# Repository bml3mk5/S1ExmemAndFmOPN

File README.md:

# Extended RAM & FM Synthesis Card for HITACHI MB-S1

This is the extension card for HITACHI MB-S1 and Limelight. This is assembled two circuits
which are extended RAMs and FM Synthesis (YAMAHA YM2203(OPN)). You can use two circuits, or just one of them.

## Used Tools

* KiCAD Version 5

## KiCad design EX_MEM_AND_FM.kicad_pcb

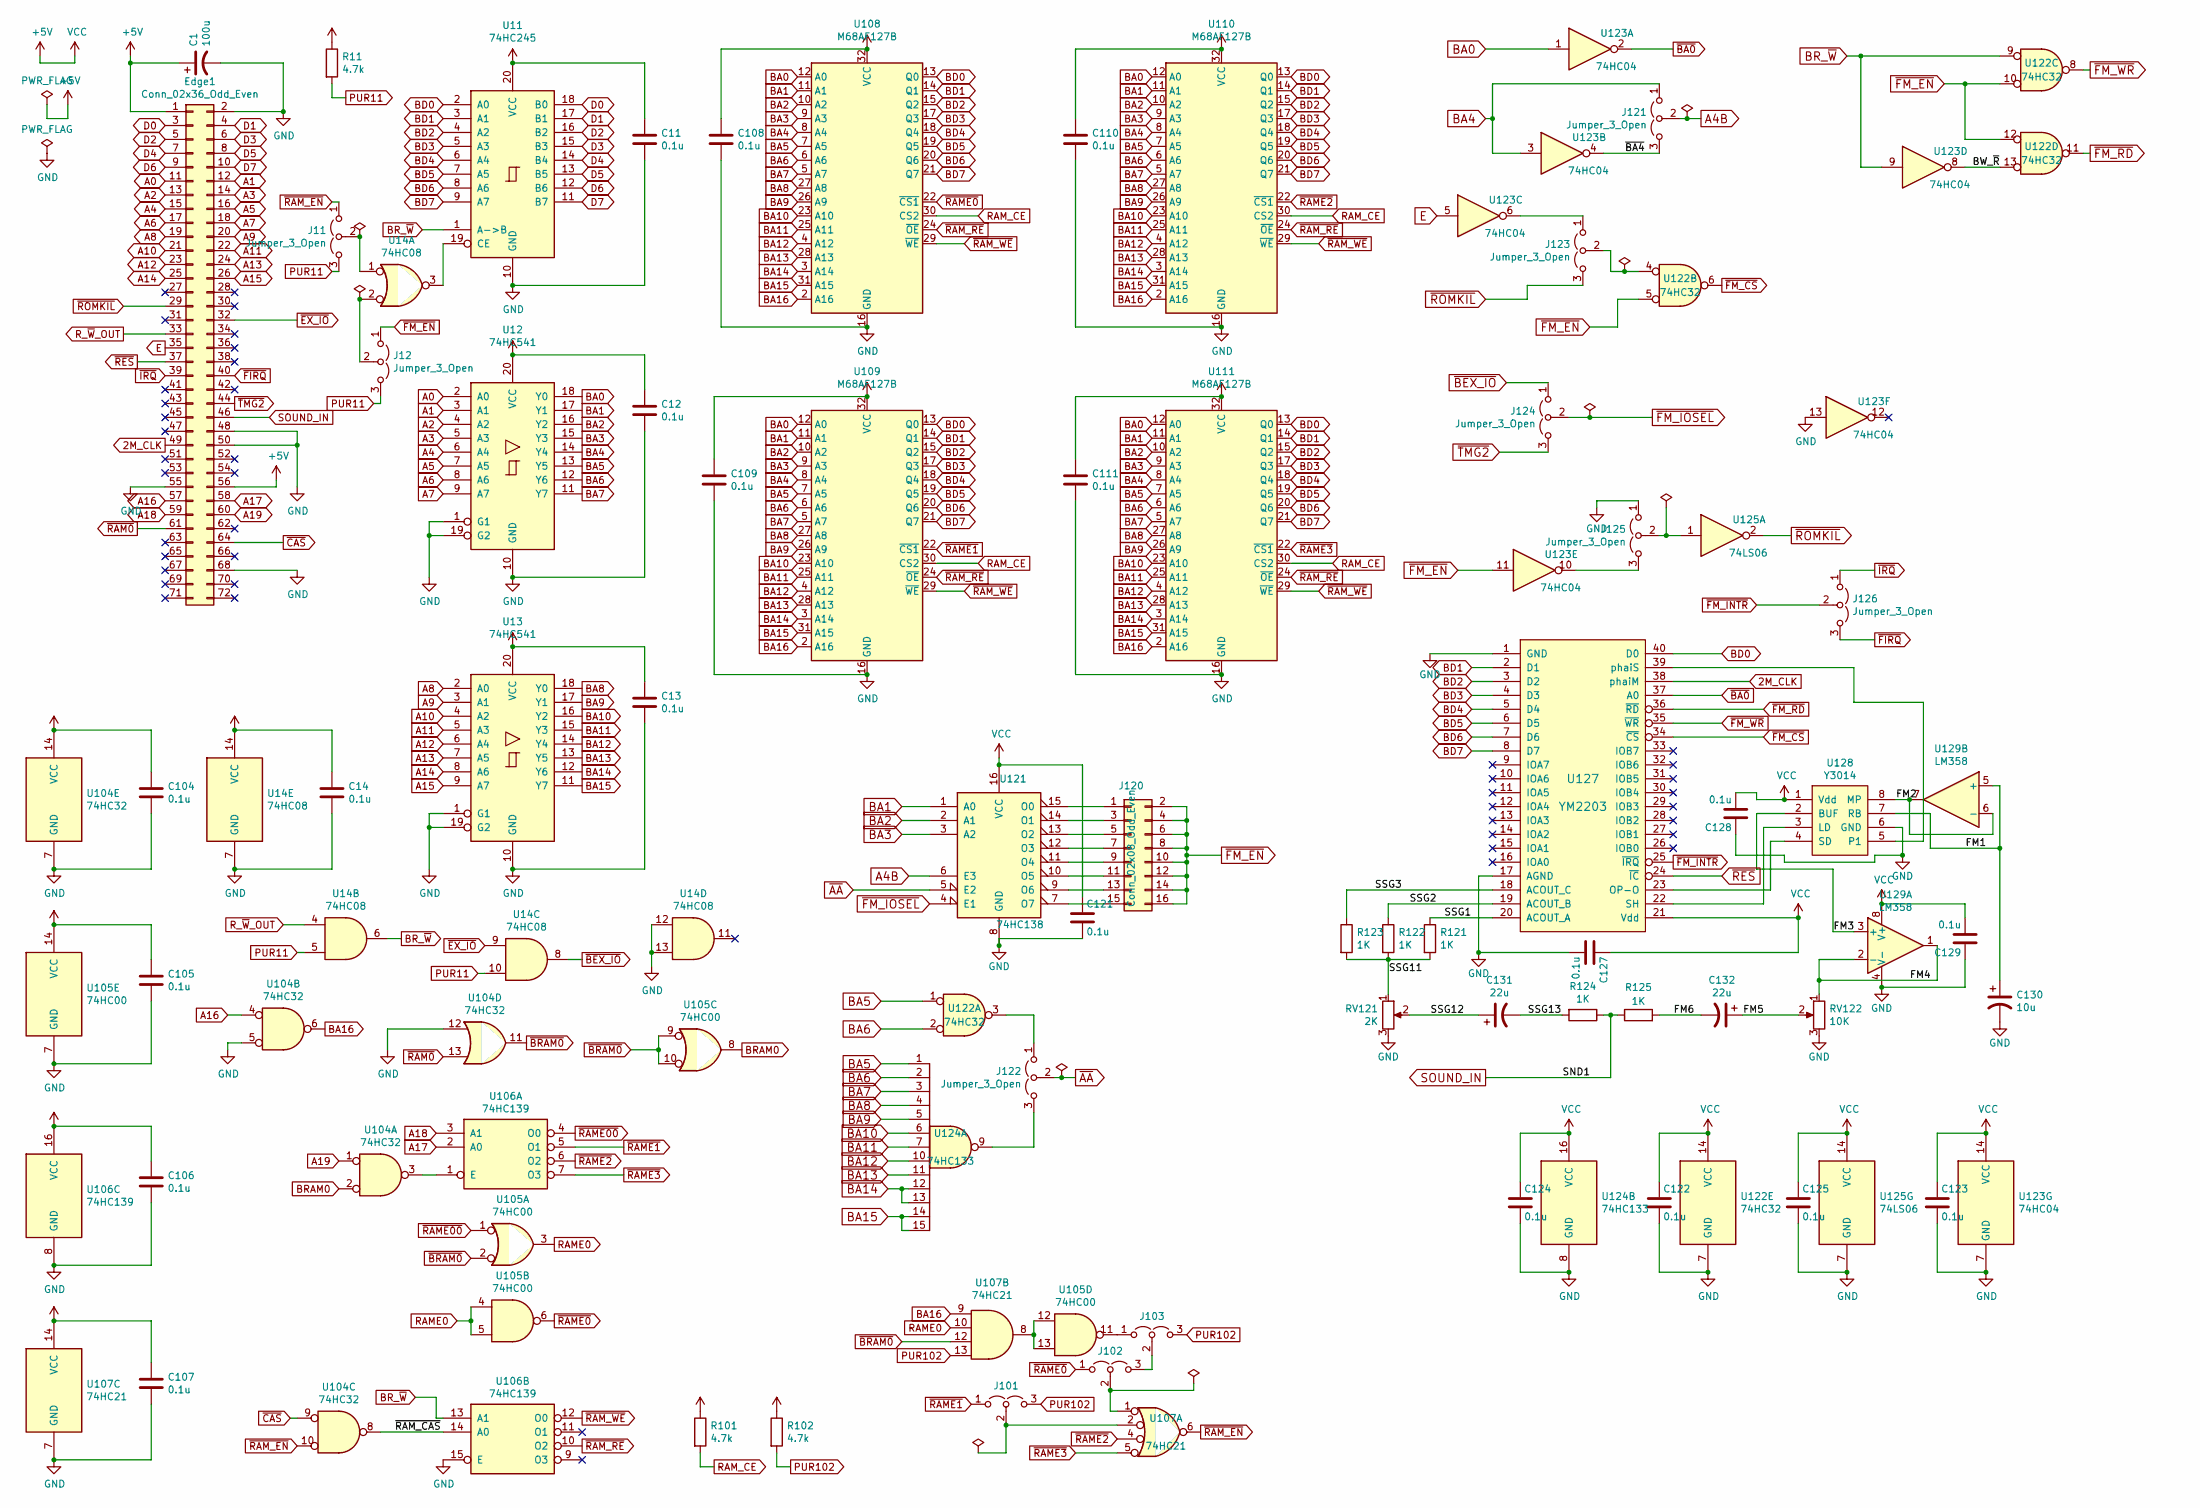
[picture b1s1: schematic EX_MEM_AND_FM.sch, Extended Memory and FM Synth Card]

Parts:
C1: 100u; CP_Radial_D6.3mm_P2.50mm
C11, C12, C13, C14, C104, C105, C106, C107, C108, C109, C110, C111, C121, C122, C123, C124, C125, C127, C128, C129: 0.1u; C_Disc_D3.0mm_W2.0mm_P2.50mm
C130: 10u; CP_Radial_D5.0mm_P2.50mm
C131, C132: 22u; CP_Radial_D5.0mm_P2.50mm
Edge1: Conn_02x36_Odd_Even; CardEdge72
J11, J12, J101, J102, J103, J121, J122, J123, J124, J125, J126: Jumper_3_Open; Pin_Header_Straight_1x03_Pitch2.54mm
J120: Conn_02x08_Odd_Even; Pin_Header_Straight_2x08_Pitch2.54mm
R11, R101, R102: 4.7k; R_Axial_DIN0204_L3.6mm_D1.6mm_P2.54mm_Vertical
R121, R122, R123, R124, R125: 1K; R_Axial_DIN0204_L3.6mm_D1.6mm_P2.54mm_Vertical
RV121: 2K; Potentiometer_Trimmer_Bourns_3339P_Horizontal
RV122: 10K; Potentiometer_Trimmer_Bourns_3339P_Horizontal
U11: 74HC245; DIP-20_W7.62mm
U12, U13: 74HC541; DIP-20_W7.62mm
U14: 74HC08; DIP-14_W7.62mm
U104, U122: 74HC32; DIP-14_W7.62mm
U105: 74HC00; DIP-14_W7.62mm
U106: 74HC139; DIP-16_W7.62mm
U107: 74HC21; DIP-14_W7.62mm
U108, U109, U110, U111: M68AF127B; SOIC-32
U121: 74HC138; DIP-16_W7.62mm
U123: 74HC04; DIP-14_W7.62mm
U124: 74HC133; DIP-16_W7.62mm
U125: 74LS06; DIP-14_W7.62mm
U127: YM2203; DIP-40_W15.24mm_Socket
U128: Y3014; DIP-8_W7.62mm_Socket
U129: LM358; DIP-8_W7.62mm_Socket

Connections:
2M_CLK: Edge1.49, U127.38 (phaiM)
+5V: C1.1, C11.1, C12.1, C13.1, C14.1, C104.1, C105.1, C106.1, C107.1, C108.1, C109.1, C110.1, C111.1, C121.1, C122.1, C123.1, C124.1, C125.1, C127.1, C128.2, C129.2, Edge1.1, Edge1.56, R11.1, R101.1, R102.1, U11.20 (VCC), U12.20 (VCC), U13.20 (VCC), U14.14 (VCC), U104.14 (VCC), U105.14 (VCC), U106.16 (VCC), U107.14 (VCC), U108.32 (VCC), U109.32 (VCC), U110.32 (VCC), U111.32 (VCC), U121.16 (VCC), U122.14 (VCC), U123.14 (VCC), U124.16 (VCC), U125.14 (VCC), U127.21 (Vdd), U128.1 (Vdd), U129.8 (V+)
/BW_~R~: U122.13, U123.8
/FM1: C130.1, U128.7 (RB), U129.5 (+)
/FM2: U128.8 (MP), U129.6 (-), U129.7
/FM3: U128.2 (BUF), U129.3 (+)
/FM4: RV122.1, U129.1, U129.2 (-)
/FM5: C132.1, RV122.2
/FM6: C132.2, R125.2
/SSG1: R121.1, U127.20 (ACOUT_A)
/SSG2: R122.1, U127.19 (ACOUT_B)
/SSG3: R123.1, U127.18 (ACOUT_C)
/SSG11: R121.2, R122.2, R123.2, RV121.1
/SSG12: C131.1, RV121.2
/SSG13: C131.2, R124.2
/~BA4: J121.3 (B), U123.4
/~RAM_CAS: U104.8, U106.14 (A0)
A0: Edge1.11, U12.2 (A0)
A1: Edge1.12, U12.3 (A1)
A2: Edge1.13, U12.4 (A2)
A3: Edge1.14, U12.5 (A3)
A4: Edge1.15, U12.6 (A4)
A4B: J121.2 (C), U121.6 (E3)
A5: Edge1.16, U12.7 (A5)
A6: Edge1.17, U12.8 (A6)
A7: Edge1.18, U12.9 (A7)
A8: Edge1.19, U13.2 (A0)
A9: Edge1.20, U13.3 (A1)
A10: Edge1.21, U13.4 (A2)
A11: Edge1.22, U13.5 (A3)
A12: Edge1.23, U13.6 (A4)
A13: Edge1.24, U13.7 (A5)
A14: Edge1.25, U13.8 (A6)
A15: Edge1.26, U13.9 (A7)
A16: Edge1.57, U104.4
A17: Edge1.58, U106.2 (A0)
A18: Edge1.59, U106.3 (A1)
A19: Edge1.60, U104.1
BA0: U12.18 (Y0), U108.12 (A0), U109.12 (A0), U110.12 (A0), U111.12 (A0), U123.1
BA1: U12.17 (Y1), U108.11 (A1), U109.11 (A1), U110.11 (A1), U111.11 (A1), U121.1 (A0)
BA2: U12.16 (Y2), U108.10 (A2), U109.10 (A2), U110.10 (A2), U111.10 (A2), U121.2 (A1)
BA3: U12.15 (Y3), U108.9 (A3), U109.9 (A3), U110.9 (A3), U111.9 (A3), U121.3 (A2)
BA4: J121.1 (A), U12.14 (Y4), U108.8 (A4), U109.8 (A4), U110.8 (A4), U111.8 (A4), U123.3
BA5: U12.13 (Y5), U108.7 (A5), U109.7 (A5), U110.7 (A5), U111.7 (A5), U122.1, U124.1
BA6: U12.12 (Y6), U108.6 (A6), U109.6 (A6), U110.6 (A6), U111.6 (A6), U122.2, U124.2
BA7: U12.11 (Y7), U108.5 (A7), U109.5 (A7), U110.5 (A7), U111.5 (A7), U124.3
BA8: U13.18 (Y0), U108.27 (A8), U109.27 (A8), U110.27 (A8), U111.27 (A8), U124.4
BA9: U13.17 (Y1), U108.26 (A9), U109.26 (A9), U110.26 (A9), U111.26 (A9), U124.5
BA10: U13.16 (Y2), U108.23 (A10), U109.23 (A10), U110.23 (A10), U111.23 (A10), U124.6
BA11: U13.15 (Y3), U108.25 (A11), U109.25 (A11), U110.25 (A11), U111.25 (A11), U124.7
BA12: U13.14 (Y4), U108.4 (A12), U109.4 (A12), U110.4 (A12), U111.4 (A12), U124.10
BA13: U13.13 (Y5), U108.28 (A13), U109.28 (A13), U110.28 (A13), U111.28 (A13), U124.11
BA14: U13.12 (Y6), U108.3 (A14), U109.3 (A14), U110.3 (A14), U111.3 (A14), U124.12, U124.13
BA15: U13.11 (Y7), U108.31 (A15), U109.31 (A15), U110.31 (A15), U111.31 (A15), U124.14, U124.15
BA16: U104.6, U107.9, U108.2 (A16), U109.2 (A16), U110.2 (A16), U111.2 (A16)
BD0: U11.2 (A0), U108.13 (Q0), U109.13 (Q0), U110.13 (Q0), U111.13 (Q0), U127.40 (D0)
BD1: U11.3 (A1), U108.14 (Q1), U109.14 (Q1), U110.14 (Q1), U111.14 (Q1), U127.2 (D1)
BD2: U11.4 (A2), U108.15 (Q2), U109.15 (Q2), U110.15 (Q2), U111.15 (Q2), U127.3 (D2)
BD3: U11.5 (A3), U108.17 (Q3), U109.17 (Q3), U110.17 (Q3), U111.17 (Q3), U127.4 (D3)
BD4: U11.6 (A4), U108.18 (Q4), U109.18 (Q4), U110.18 (Q4), U111.18 (Q4), U127.5 (D4)
BD5: U11.7 (A5), U108.19 (Q5), U109.19 (Q5), U110.19 (Q5), U111.19 (Q5), U127.6 (D5)
BD6: U11.8 (A6), U108.20 (Q6), U109.20 (Q6), U110.20 (Q6), U111.20 (Q6), U127.7 (D6)
BD7: U11.9 (A7), U108.21 (Q7), U109.21 (Q7), U110.21 (Q7), U111.21 (Q7), U127.8 (D7)
BRAM0: U104.2, U105.8
BR_~W: U11.1 (A->B), U14.6, U106.13 (A1), U122.9, U123.9
D0: Edge1.3, U11.18 (B0)
D1: Edge1.4, U11.17 (B1)
D2: Edge1.5, U11.16 (B2)
D3: Edge1.6, U11.15 (B3)
D4: Edge1.7, U11.14 (B4)
D5: Edge1.8, U11.13 (B5)
D6: Edge1.9, U11.12 (B6)
D7: Edge1.10, U11.11 (B7)
E: Edge1.35, U123.5
GND: C1.2, C11.2, C12.2, C13.2, C14.2, C104.2, C105.2, C106.2, C107.2, C108.2, C109.2, C110.2, C111.2, C121.2, C122.2, C123.2, C124.2, C125.2, C127.2, C128.1, C129.1, C130.2, Edge1.2, Edge1.48, Edge1.50, Edge1.55, Edge1.68, J125.1 (A), RV121.3, RV122.3, U11.10 (GND), U12.1 (G1), U12.10 (GND), U12.19 (G2), U13.1 (G1), U13.10 (GND), U13.19 (G2), U14.7 (GND), U14.12, U14.13, U104.5, U104.7 (GND), U104.12, U105.7 (GND), U106.8 (GND), U106.15 (E), U107.7 (GND), U108.16 (GND), U109.16 (GND), U110.16 (GND), U111.16 (GND), U121.8 (GND), U122.7 (GND), U123.7 (GND), U123.13, U124.8 (GND), U125.7 (GND), U127.1 (GND), U127.17 (AGND), U128.6 (GND), U129.4 (V-)
unnamed: J11.2 (C), U14.1
unnamed: J12.2 (C), U14.2
unnamed: J101.2 (C), U107.2
unnamed: J102.2 (C), U107.1
unnamed: J102.3 (B), J103.2 (C)
unnamed: J103.1 (A), U105.11
unnamed: J120.1, U121.15 (O0)
unnamed: J120.3, U121.14 (O1)
unnamed: J120.5, U121.13 (O2)
unnamed: J120.7, U121.12 (O3)
unnamed: J120.9, U121.11 (O4)
unnamed: J120.11, U121.10 (O5)
unnamed: J120.13, U121.9 (O6)
unnamed: J120.15, U121.7 (O7)
unnamed: J122.1 (A), U122.3
unnamed: J122.3 (B), U124.9
unnamed: J123.1 (A), U123.6
unnamed: J123.2 (C), U122.4
unnamed: J125.2 (C), U125.1
unnamed: J125.3 (B), U123.10
unnamed: U11.19 (CE), U14.3
unnamed: U104.3, U106.1 (E)
unnamed: U105.12, U105.13, U107.8
unnamed: U127.22 (SH), U128.3 (LD)
unnamed: U127.23 (OP-O), U128.4 (SD)
unnamed: U127.39 (phaiS), U128.5 (P1)
PUR11: J11.3 (B), J12.3 (B), R11.2, U14.5, U14.10
PUR102: J101.3 (B), J103.3 (B), R102.2, U107.13
RAME0: U105.3, U105.4, U105.5, U107.10
RAM_CE: R101.2, U108.30 (CS2), U109.30 (CS2), U110.30 (CS2), U111.30 (CS2)
R_~W~_OUT: Edge1.33, U14.4
SOUND_IN: Edge1.46, R124.1, R125.1
~AA: J122.2 (C), U121.5 (E2)
~BA0: U123.2, U127.37 (A0)
~BEX_IO: J124.1 (A), U14.8
~BRAM0: U104.11, U105.2, U105.9, U105.10, U107.12
~CAS: Edge1.64, U104.9
~EX_IO: Edge1.32, U14.9
~FIRQ: Edge1.40, J126.3 (B)
~FM_CS: U122.6, U127.34 (~CS)
~FM_EN: J12.1 (A), J120.2, J120.4, J120.6, J120.8, J120.10, J120.12, J120.14, J120.16, U122.5, U122.10, U122.12, U123.11
~FM_INTR: J126.2 (C), U127.25 (~IRQ)
~FM_IOSEL: J124.2 (C), U121.4 (E1)
~FM_RD: U122.11, U127.36 (~RD)
~FM_WR: U122.8, U127.35 (~WR)
~IRQ: Edge1.39, J126.1 (A)
~RAM0: Edge1.61, U104.13
~RAME00: U105.1, U106.4 (O0)
~RAME0: J102.1 (A), U105.6, U108.22 (~CS1)
~RAME1: J101.1 (A), U106.5 (O1), U109.22 (~CS1)
~RAME2: U106.6 (O2), U107.4, U110.22 (~CS1)
~RAME3: U106.7 (O3), U107.5, U111.22 (~CS1)
~RAM_EN: J11.1 (A), U104.10, U107.6
~RAM_RE: U106.10 (O2), U108.24 (~OE), U109.24 (~OE), U110.24 (~OE), U111.24 (~OE)
~RAM_WE: U106.12 (O0), U108.29 (~WE), U109.29 (~WE), U110.29 (~WE), U111.29 (~WE)
~RES: Edge1.37, U127.24 (~IC)
~ROMKIL: Edge1.29, J123.3 (B), U125.2
~TMG2: Edge1.44, J124.3 (B)

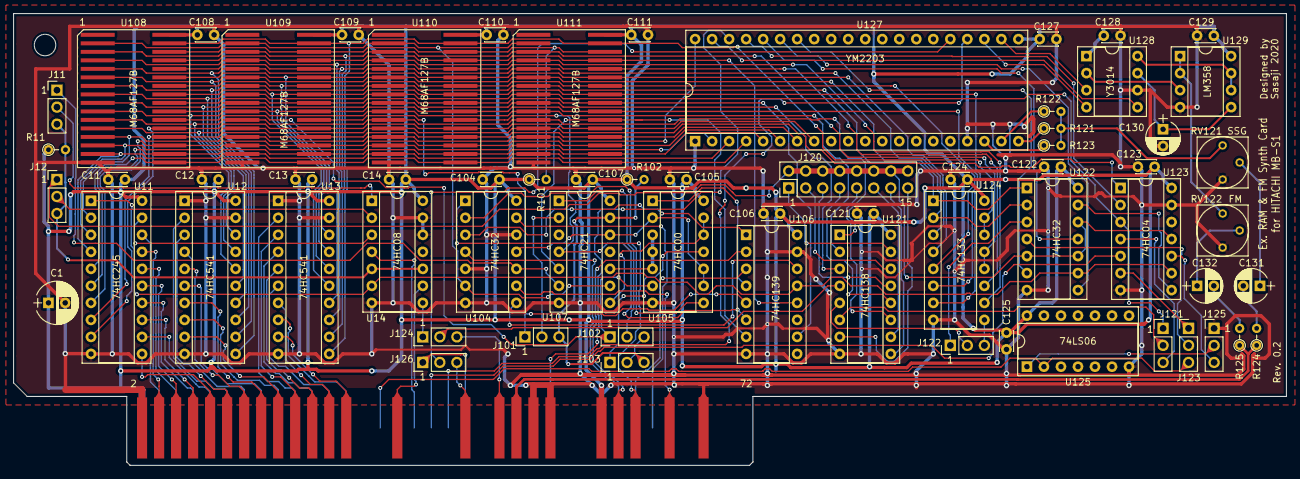
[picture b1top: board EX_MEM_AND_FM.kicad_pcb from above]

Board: 2 copper layers, 190.0 x 67.4 mm, 67 parts (0 on the bottom side), 133 nets.

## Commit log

2023-03-01 Revision 0.2
2023-07-09 Add an images
